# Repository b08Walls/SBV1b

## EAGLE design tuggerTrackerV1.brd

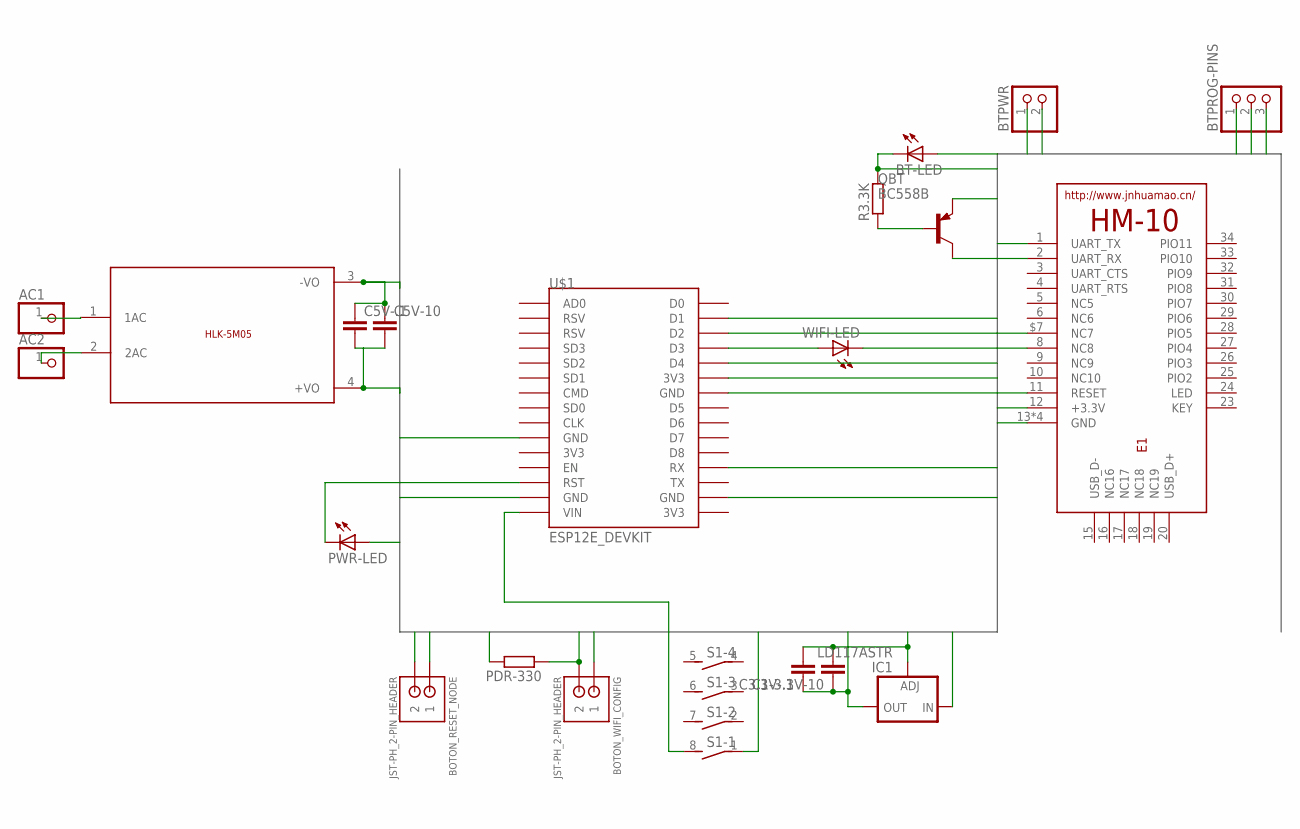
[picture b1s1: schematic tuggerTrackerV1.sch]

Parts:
AC1, AC2: PINHD-1X1; 1X01
BOTON_RESET_NODE: JST-PH_2-PIN_HEADER; JST_B2B-PH_HEADER
BOTON_WIFI_CONFIG: JST-PH_2-PIN_HEADER; JST_B2B-PH_HEADER
BT-LED: LEDCHIPLED_1206; CHIPLED_1206
BTPROG-PINS: PINHD-1X3; 1X03
BTPWR: PINHD-1X2; 1X02
C1-3.3V-10, C3.3V-.1, C5V-10, C5V-.1: CC0603; C0603
E1: HM-10-BOARD; 26.9X13X2.2_BOARD
IC1: LD117ASTR; SOT223
PDR-330: RR1206; R1206
PWR-LED: LEDCHIPLED_1206; CHIPLED_1206
QBT: BC558B; TO92-EBC
R3.3K: RR1206; R1206
S1: DIP04S
U$1: ESP12E_DEVKIT
U$2: 5VDC/5W; HLK-5M05
WIFI-LED: LEDCHIPLED_1206; CHIPLED_1206

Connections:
BTPG1: BTPROG-PINS.1, E1.$7 (NC7)
BTPG2: BTPROG-PINS.2, E1.8 (NC8)
BTRST: BTPROG-PINS.3, E1.11 (RESET)
BTVCC: E1.12 (+3.3V), QBT.C
D1: BT-LED.C, R3.3K.2, U$1.D1
D2: BOTON_WIFI_CONFIG.P2 (2), PDR-330.1, U$1.D2
GND: BOTON_RESET_NODE.P2 (2), BTPWR.1, C1-3.3V-10.2, C3.3V-.1.2, C5V-10.1, C5V-.1.1, E1.13 (GND), E1.14 (GND), E1.21 (GND), E1.22 (GND), IC1.1 (ADJ), PDR-330.2, PWR-LED.C, U$1.GND@0 (GND), U$1.GND@1 (GND), U$1.GND@2 (GND), U$1.GND@3 (GND), U$2.3 (-VO), WIFI-LED.C
unnamed: QBT.B, R3.3K.1
unnamed: AC1.1, U$2.1 (1AC)
unnamed: S1.8 (2), U$1.VIN
unnamed: AC2.1, U$2.2 (2AC)
unnamed: U$1.D3, WIFI-LED.A
NODRST: BOTON_RESET_NODE.P1 (1), U$1.RST
NRXBTX: E1.1 (UART_TX), U$1.RX
NTXBRX: E1.2 (UART_RX), U$1.D4
V3NODE: BOTON_WIFI_CONFIG.P1 (1), BT-LED.A, PWR-LED.A, U$1.3V3@1 (3V3)
V3REG: C1-3.3V-10.1, C3.3V-.1.1, IC1.4 (OUT), QBT.E
VIN: BTPWR.2, C5V-10.2, C5V-.1.2, IC1.3 (IN), S1.1, U$2.4 (+VO)

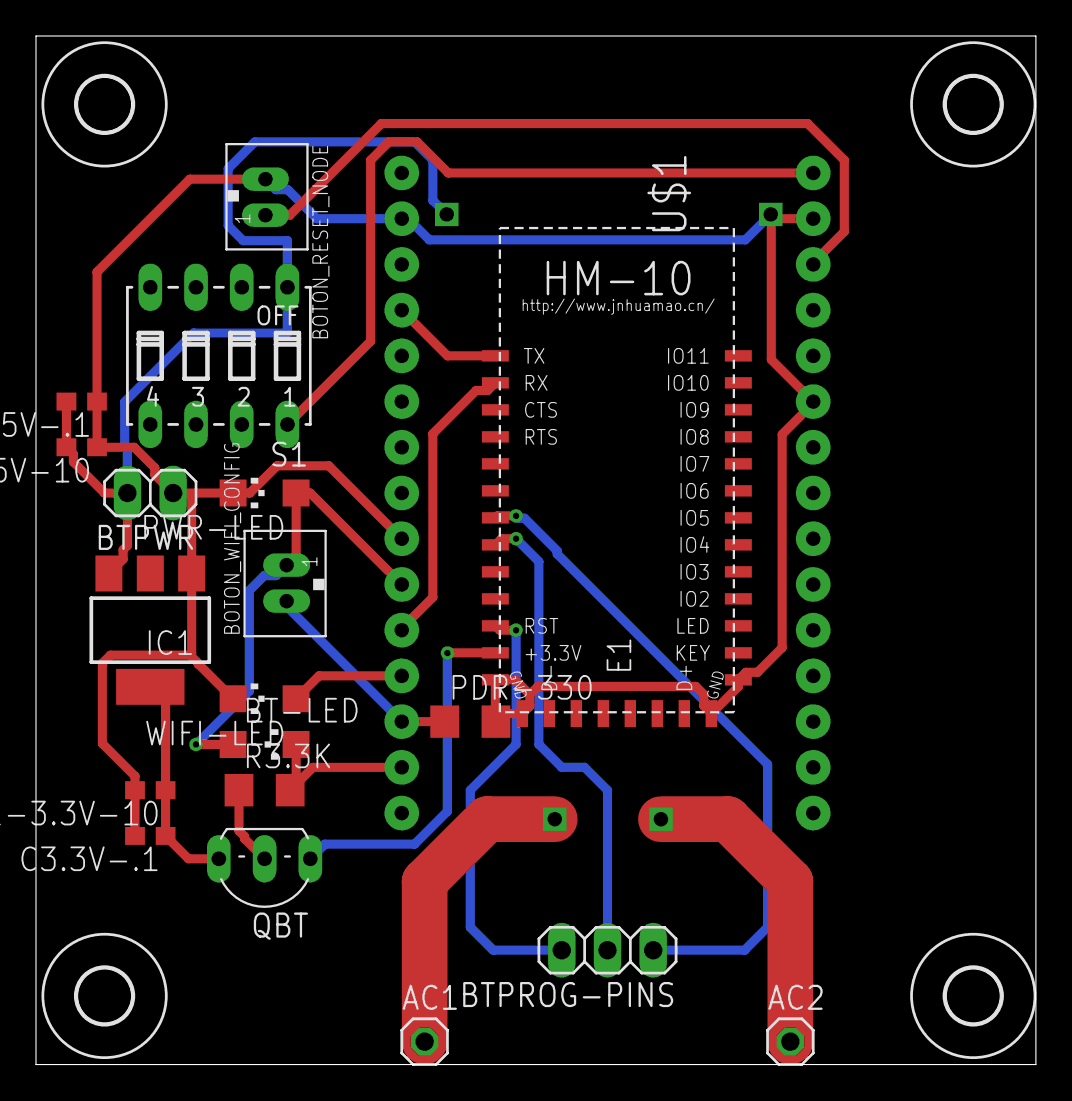
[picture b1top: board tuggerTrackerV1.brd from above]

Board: 2 copper layers, 55.5 x 57.1 mm, 25 parts (1 on the bottom side), 18 nets.

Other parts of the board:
U$6, U$7, U$8, U$9: 3,0

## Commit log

2018-04-12 jojo
2018-04-13 eagle
2018-05-13 cambios
